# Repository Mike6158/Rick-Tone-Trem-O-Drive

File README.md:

# Rick-Tone-Trem-O-Drive
Vintage drive and tremolo circuit on a circuit board

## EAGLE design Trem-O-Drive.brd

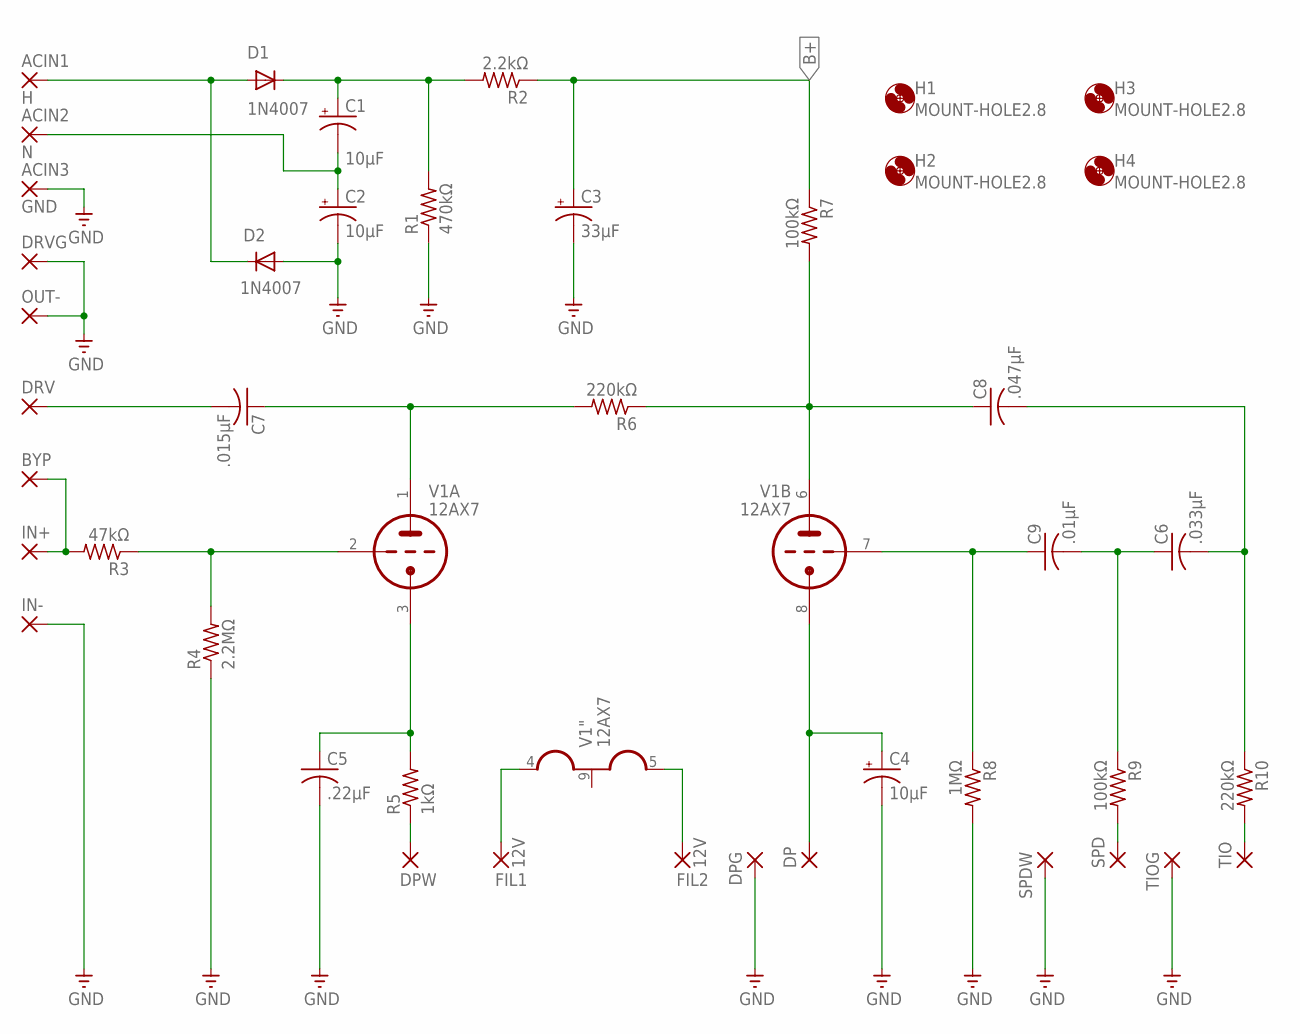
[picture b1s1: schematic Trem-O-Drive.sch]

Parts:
ACIN1: H; 3,81/1,4
ACIN2: N; 3,81/1,4
ACIN3: GND; 3,81/1,4
BYP: 3,81/1,4
C1, C2, C4: 10µF; E5-10,5
C3: 33µF; E5-10,5
C5: .22µF; C150-064X183
C6: .033µF; C102-064X133
C7: .015µF; C102-064X133
C8: .047µF; C102-064X133
C9: .01µF; C102-064X133
D1, D2: 1N4007; DIODE-1N4148
DP: 3,81/1,4
DPG: 3,81/1,4
DPW: 3,81/1,4
DRV: 3,81/1,4
DRVG: 3,81/1,4
FIL1, FIL2: 12V; 3,81/1,4
H1, H2, H3, H4: MOUNT-HOLE2.8; 2,8
IN+: 3,81/1,4
IN-: 3,81/1,4
OUT-: 3,81/1,4
R1: 470kΩ; 0411/12
R2: 2.2kΩ; 0411/12
R3: 47kΩ; 0411/12
R4: 2.2MΩ; 0411/12
R5: 1kΩ; 0411/12
R6, R10: 220kΩ; 0411/12
R7, R9: 100kΩ; 0411/12
R8: 1MΩ; 0411/12
SPD: 3,81/1,4
SPDW: 3,81/1,4
TIO: 3,81/1,4
TIOG: 3,81/1,4
V1: 12AX7; NOVAL

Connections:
B+: C3.+, R2.1, R7.1
FIL1: FIL1.1, V1.4 (H1)
FIL2: FIL2.1, V1.5 (H3)
GND: ACIN3.1, C2.-, C3.-, C4.-, C5.2, D2.A, DPG.1, DRVG.1, IN-.1, OUT-.1, R1.1, R4.1, R8.2, SPDW.1, TIOG.1
unnamed: ACIN1.1, D1.A, D2.C
unnamed: C1.+, D1.C, R1.2, R2.2
unnamed: ACIN2.1, C1.-, C2.+
unnamed: C4.+, DP.1, V1.8 (TK)
unnamed: DPW.1, R5.1
unnamed: C9.1, R8.1, V1.7 (TG)
unnamed: C6.1, C9.2, R9.1
unnamed: C6.2, C8.2, R10.1
unnamed: R9.2, SPD.1
unnamed: R3.1, R4.2, V1.2 (TG)
unnamed: C7.2, DRV.1
unnamed: C7.1, R6.2, V1.1 (TA)
unnamed: C8.1, R6.1, R7.2, V1.6 (TA)
unnamed: R10.2, TIO.1
unnamed: BYP.1, IN+.1, R3.2
unnamed: C5.1, R5.2, V1.3 (TK)

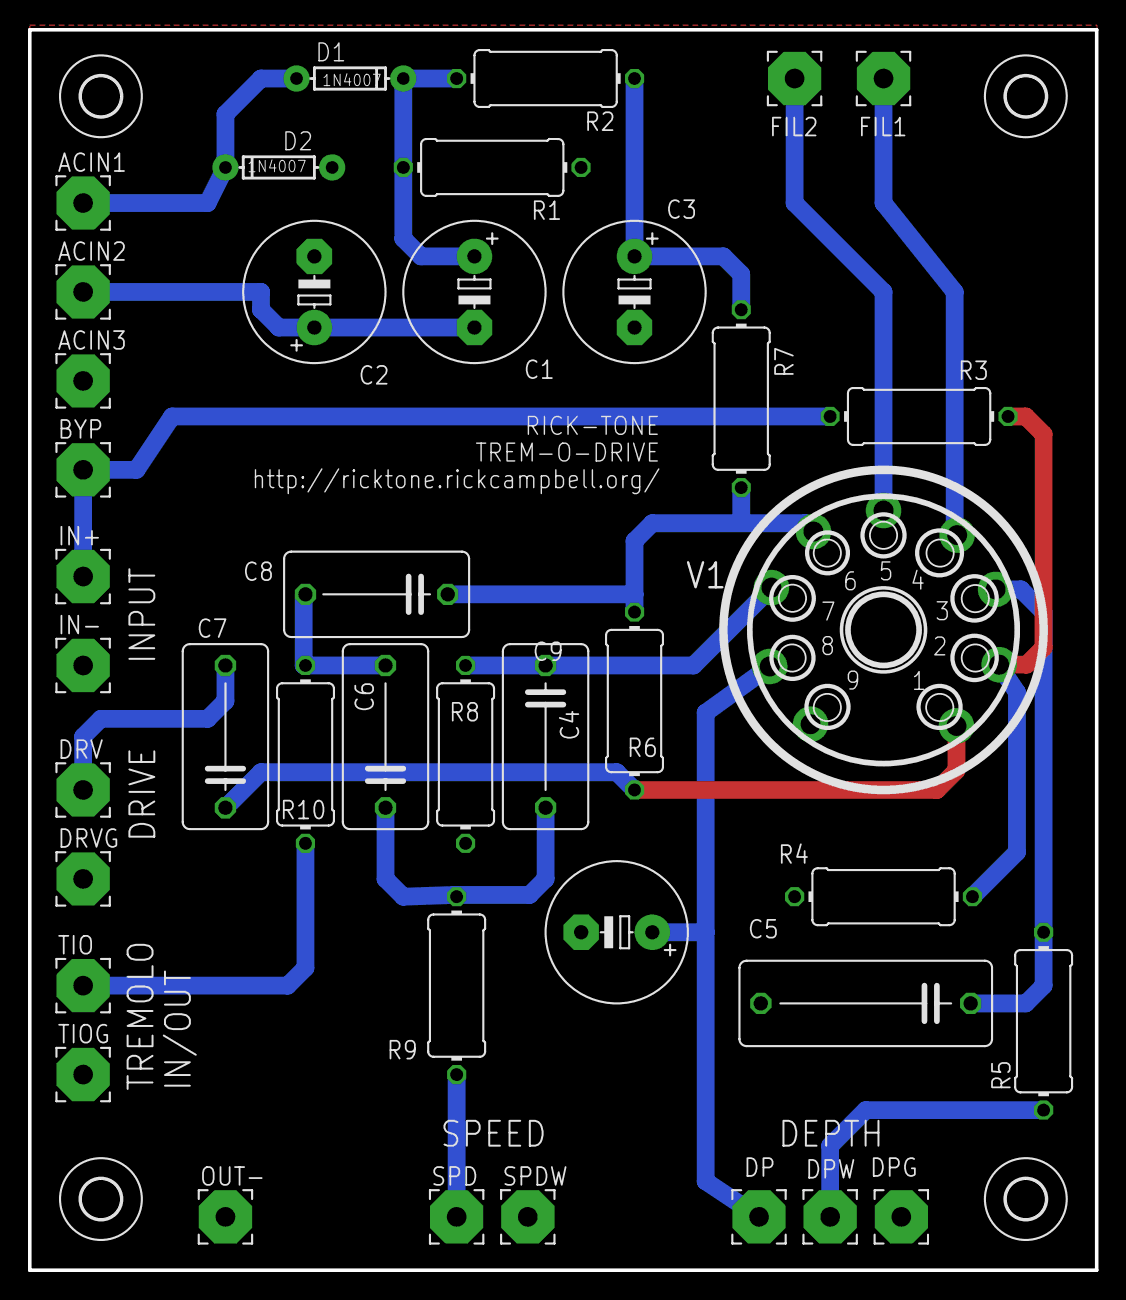
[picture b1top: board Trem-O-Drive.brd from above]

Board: 2 copper layers, 76.2 x 88.6 mm, 44 parts (0 on the bottom side), 20 nets.

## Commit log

2016-11-11 Created project and added files
    This project entails converting a vintage drive and tremolo circuit from point to point wiring to a circuit board. The project involves working with 120VAC, high DC voltages (280VDC), and a 12AX7 tub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
    Files include the original build instructions combined into one PDF file, the Cadsoft Eagle files that I created, and some photos of a prototype circuit board that I built (including some testing ima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

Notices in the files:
parts and their libraries:
SparkFun-DiscreteSemi: Licensing: Creative Commons ShareAlike 4.0 International - https://creativecommons.org/licenses/by-sa/4.0
